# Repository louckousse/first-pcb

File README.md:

# FLATBRAIN
My first PCB, inspired by the Kyria from [Splitkb](https://splitkb.com) and the [Atreus](https://github.com/technomancy/atreus).
The goal is to get an unsplitted Kyria easily transportable.
The angle is 28° which approximatively correspond to my hand angle.

All the pcb files are created in Kicad, you can find everything in the root folder.

All the dxf files are created in Freecad, you can find everything in the case folder.
For now there is only file necessary to create pcb plate, and the kicad project associated.

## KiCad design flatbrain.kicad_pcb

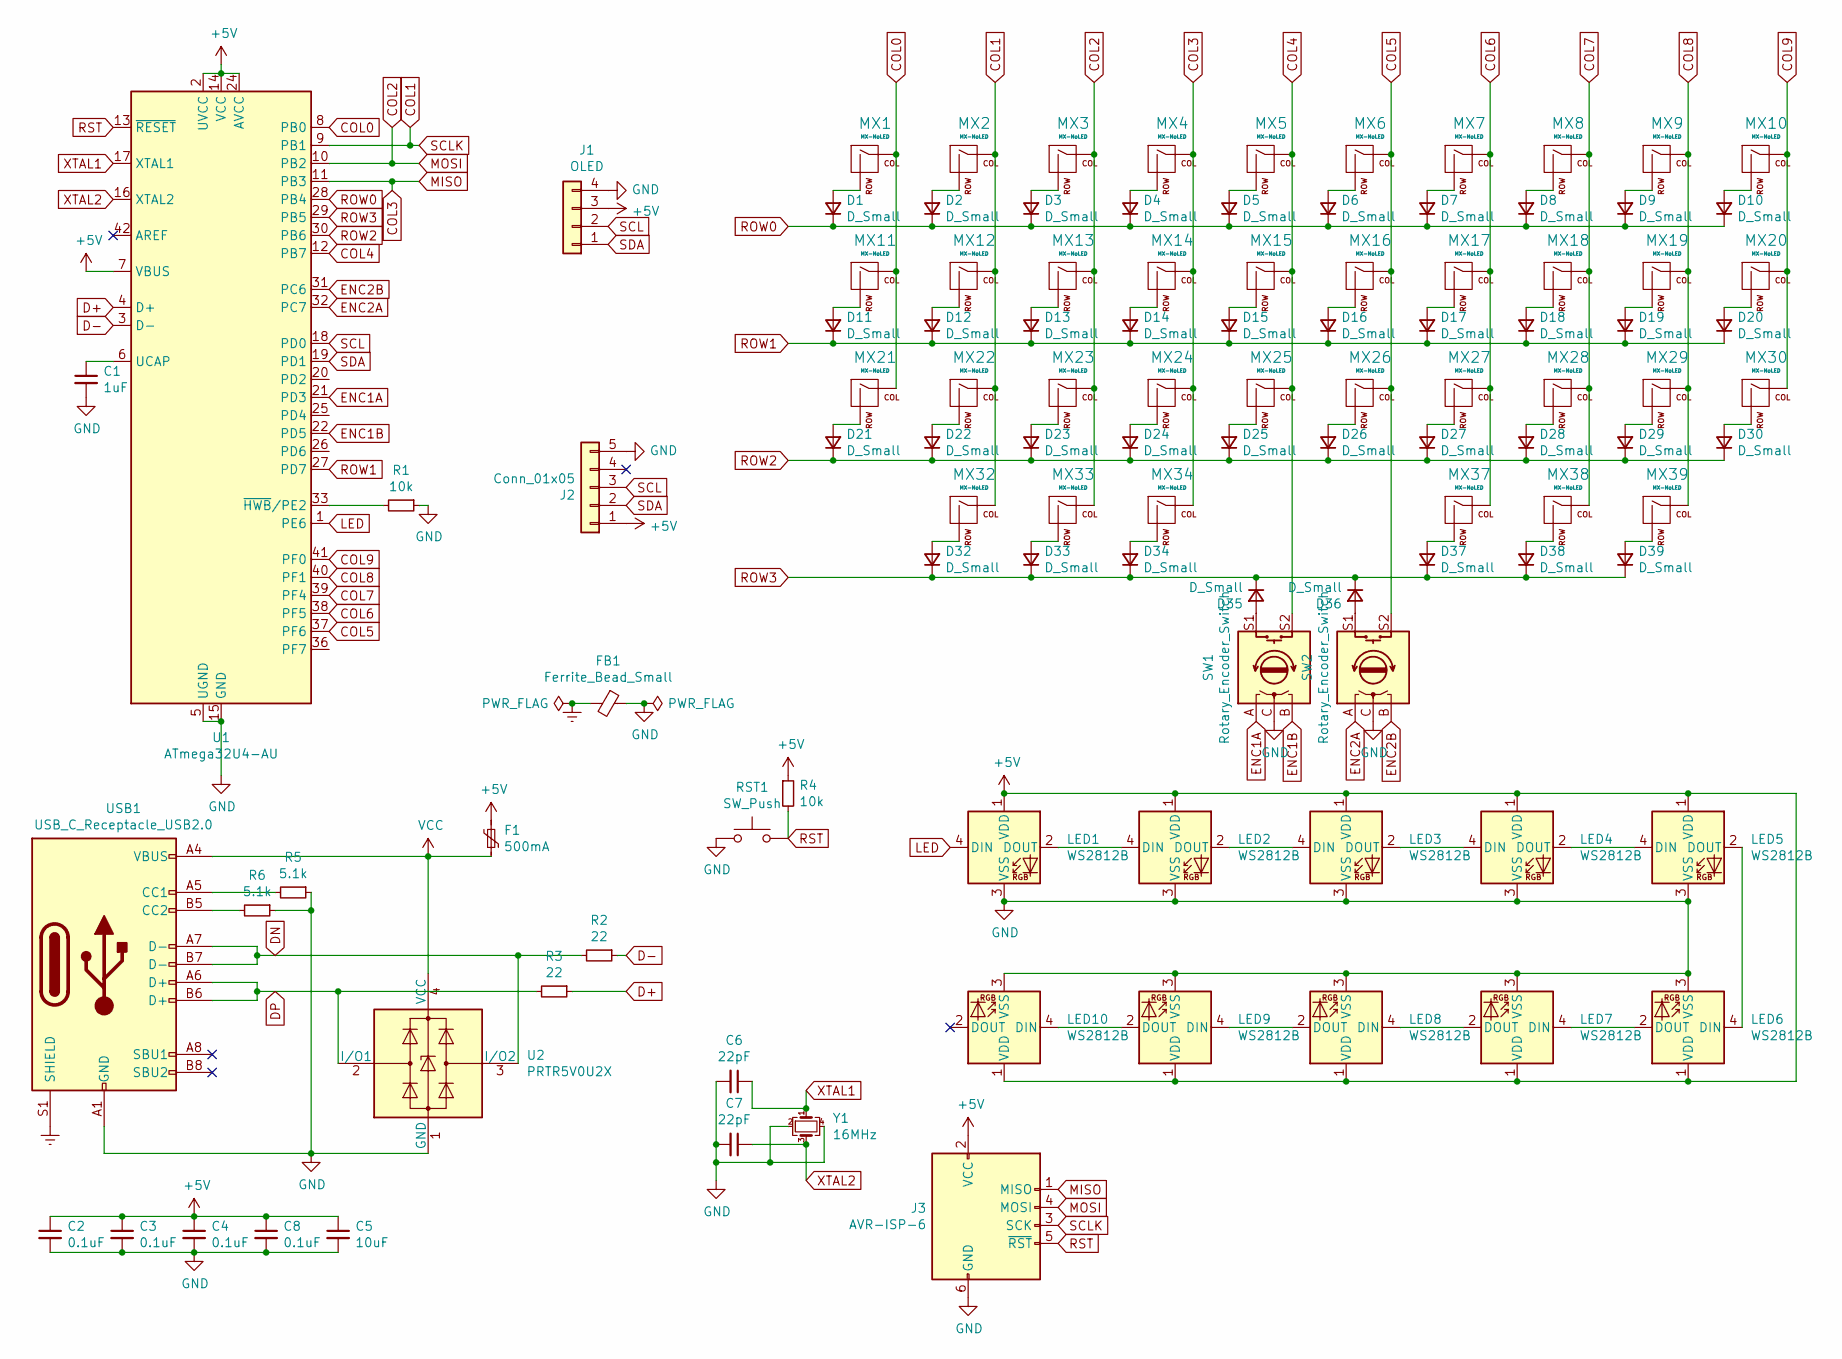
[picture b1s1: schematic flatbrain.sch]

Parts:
C1: 1uF; C_0805_2012Metric
C2, C3, C4, C8: 0.1uF; C_0805_2012Metric
C5: 10uF; C_0805_2012Metric
C6, C7: 22pF; C_0805_2012Metric
D1, D2, D3, D4, D5, D6, D7, D8, D9, D10, D11, D12, D13, D14, D15, D16, D17, D18, D19, D20, D21, D22, D23, D24, D25, D26, D27, D28, D29, D30, D32, D33, D34, D35, D36, D37, D38, D39: D_Small; Diode-Hybrid-Back
F1: 500mA; Fuse_1206_3216Metric
FB1: Ferrite_Bead_Small; L_0805_2012Metric_Pad1.15x1.40mm_HandSolder
J1: OLED; PinHeader_1x04_P2.54mm_Vertical
J2: Conn_01x05; pimoroni_trackball
J3: AVR-ISP-6; Reset_Pretty-Mask
LED1, LED2, LED3, LED4, LED5, LED6, LED7, LED8, LED9, LED10: WS2812B; LED_WS2812B_PLCC4_5.0x5.0mm_P3.2mm
MX1, MX2, MX3, MX4, MX5, MX6, MX7, MX8, MX9, MX10, MX11, MX12, MX13, MX14, MX15, MX16, MX17, MX18, MX19, MX20, MX21, MX22, MX23, MX24, MX25, MX26, MX27, MX28, MX29, MX30, MX32, MX33, MX34, MX37, MX38, MX39: MX-NoLED; mix_1u
R1, R4: 10k; R_0805_2012Metric
R2, R3: 22; R_0805_2012Metric
R5, R6: 5.1k; R_0805_2012Metric
RST1: SW_Push; SKQG-1155865
SW1, SW2: Rotary_Encoder_Switch; rotary_full
U1: ATmega32U4-AU; TQFP-44_10x10mm_P0.8mm
U2: PRTR5V0U2X; SOT143B
USB1: USB_C_Receptacle_USB2.0; USB_C_Receptacle_HRO_TYPE-C-31-M-12
Y1: 16MHz; Crystal_SMD_3225-4Pin_3.2x2.5mm

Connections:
+5V: C2.1, C3.1, C4.1, C5.1, C8.1, F1.1, J1.3, J2.1, J3.2 (VCC), LED1.1 (VDD), LED2.1 (VDD), LED3.1 (VDD), LED4.1 (VDD), LED5.1 (VDD), LED6.1 (VDD), LED7.1 (VDD), LED8.1 (VDD), LED9.1 (VDD), LED10.1 (VDD), R4.1, U1.2 (UVCC), U1.7 (VBUS), U1.14 (VCC), U1.24 (AVCC), U1.34 (VCC), U1.44 (AVCC); also elsewhere on the board
COL0: MX1.1 (COL), MX11.1 (COL), MX21.1 (COL), U1.8 (PB0)
COL1: J3.3 (SCK), MX2.1 (COL), MX12.1 (COL), MX22.1 (COL), MX32.1 (COL), U1.9 (PB1)
COL2: J3.4 (MOSI), MX3.1 (COL), MX13.1 (COL), MX23.1 (COL), MX33.1 (COL), U1.10 (PB2)
COL3: J3.1 (MISO), MX4.1 (COL), MX14.1 (COL), MX24.1 (COL), MX34.1 (COL), U1.11 (PB3)
COL4: MX5.1 (COL), MX15.1 (COL), MX25.1 (COL), SW1.S2, U1.12 (PB7)
COL5: MX6.1 (COL), MX16.1 (COL), MX26.1 (COL), SW2.S2, U1.37 (PF6)
COL6: MX7.1 (COL), MX17.1 (COL), MX27.1 (COL), MX37.1 (COL), U1.38 (PF5)
COL7: MX8.1 (COL), MX18.1 (COL), MX28.1 (COL), MX38.1 (COL), U1.39 (PF4)
COL8: MX9.1 (COL), MX19.1 (COL), MX29.1 (COL), MX39.1 (COL), U1.40 (PF1)
COL9: MX10.1 (COL), MX20.1 (COL), MX30.1 (COL), U1.41 (PF0)
D+: R3.1, U1.4 (D+)
D-: R2.1, U1.3 (D-)
DN: R2.2, U2.3 (I/O2), USB1.A7 (D-), USB1.B7 (D-)
DP: R3.2, U2.2 (I/O1), USB1.A6 (D+), USB1.B6 (D+)
ENC1A: SW1.A, U1.21 (PD3)
ENC1B: SW1.B, U1.22 (PD5)
ENC2A: SW2.A, U1.32 (PC7)
ENC2B: SW2.B, U1.31 (PC6)
Earth: FB1.2, USB1.S1 (SHIELD)
GND: C1.2, C2.2, C3.2, C4.2, C5.2, C6.2, C7.2, C8.2, FB1.1, J1.4, J2.5, J3.6 (GND), LED1.3 (VSS), LED2.3 (VSS), LED3.3 (VSS), LED4.3 (VSS), LED5.3 (VSS), LED6.3 (VSS), LED7.3 (VSS), LED8.3 (VSS), LED9.3 (VSS), LED10.3 (VSS), R1.1, R5.1, R6.1, RST1.1, SW1.C, SW2.C, U1.5 (UGND), U1.15 (GND), U1.23 (GND), U1.35 (GND), U1.43 (GND), U2.1 (GND), USB1.A1 (GND), USB1.A12 (GND), USB1.B1 (GND), USB1.B12 (GND), Y1.2, Y1.4; also elsewhere on the board
LED: LED1.4 (DIN), U1.1 (PE6)
unnamed: C1.1, U1.6 (UCAP)
unnamed: D1.2 (A), MX1.2 (ROW)
unnamed: D2.2 (A), MX2.2 (ROW)
unnamed: D3.2 (A), MX3.2 (ROW)
unnamed: D4.2 (A), MX4.2 (ROW)
unnamed: D5.2 (A), MX5.2 (ROW)
unnamed: D6.2 (A), MX6.2 (ROW)
unnamed: D7.2 (A), MX7.2 (ROW)
unnamed: D8.2 (A), MX8.2 (ROW)
unnamed: D9.2 (A), MX9.2 (ROW)
unnamed: D10.2 (A), MX10.2 (ROW)
unnamed: D11.2 (A), MX11.2 (ROW)
unnamed: D12.2 (A), MX12.2 (ROW)
unnamed: D13.2 (A), MX13.2 (ROW)
unnamed: D14.2 (A), MX14.2 (ROW)
unnamed: D15.2 (A), MX15.2 (ROW)
unnamed: D16.2 (A), MX16.2 (ROW)
unnamed: D17.2 (A), MX17.2 (ROW)
unnamed: D18.2 (A), MX18.2 (ROW)
unnamed: D19.2 (A), MX19.2 (ROW)
unnamed: D20.2 (A), MX20.2 (ROW)
unnamed: D21.2 (A), MX21.2 (ROW)
unnamed: D22.2 (A), MX22.2 (ROW)
unnamed: D23.2 (A), MX23.2 (ROW)
unnamed: D24.2 (A), MX24.2 (ROW)
unnamed: D25.2 (A), MX25.2 (ROW)
unnamed: D26.2 (A), MX26.2 (ROW)
unnamed: D27.2 (A), MX27.2 (ROW)
unnamed: D28.2 (A), MX28.2 (ROW)
unnamed: D29.2 (A), MX29.2 (ROW)
unnamed: D30.2 (A), MX30.2 (ROW)
unnamed: D32.2 (A), MX32.2 (ROW)
unnamed: D33.2 (A), MX33.2 (ROW)
unnamed: D34.2 (A), MX34.2 (ROW)
unnamed: D35.2 (A), SW1.S1
unnamed: D36.2 (A), SW2.S1
unnamed: D37.2 (A), MX37.2 (ROW)
unnamed: D38.2 (A), MX38.2 (ROW)
unnamed: D39.2 (A), MX39.2 (ROW)
unnamed: LED1.2 (DOUT), LED2.4 (DIN)
unnamed: LED2.2 (DOUT), LED3.4 (DIN)
unnamed: LED3.2 (DOUT), LED4.4 (DIN)
unnamed: LED4.2 (DOUT), LED5.4 (DIN)
unnamed: LED5.2 (DOUT), LED6.4 (DIN)
unnamed: LED6.2 (DOUT), LED7.4 (DIN)
unnamed: LED7.2 (DOUT), LED8.4 (DIN)
unnamed: LED8.2 (DOUT), LED9.4 (DIN)
unnamed: LED9.2 (DOUT), LED10.4 (DIN)
unnamed: R1.2, U1.33 (~HWB~/PE2)
unnamed: R5.2, USB1.A5 (CC1)
unnamed: R6.2, USB1.B5 (CC2)
ROW0: D1.1 (K), D2.1 (K), D3.1 (K), D4.1 (K), D5.1 (K), D6.1 (K), D7.1 (K), D8.1 (K), D9.1 (K), D10.1 (K), U1.28 (PB4)
ROW1: D11.1 (K), D12.1 (K), D13.1 (K), D14.1 (K), D15.1 (K), D16.1 (K), D17.1 (K), D18.1 (K), D19.1 (K), D20.1 (K), U1.27 (PD7)
ROW2: D21.1 (K), D22.1 (K), D23.1 (K), D24.1 (K), D25.1 (K), D26.1 (K), D27.1 (K), D28.1 (K), D29.1 (K), D30.1 (K), U1.30 (PB6)
ROW3: D32.1 (K), D33.1 (K), D34.1 (K), D35.1 (K), D36.1 (K), D37.1 (K), D38.1 (K), D39.1 (K), U1.29 (PB5)
RST: J3.5 (~RST), R4.2, RST1.2, U1.13 (~RESET)
SCL: J1.2, J2.3, U1.18 (PD0); also elsewhere on the board
SDA: J1.1, J2.2, U1.19 (PD1); also elsewhere on the board
VCC: F1.2, U2.4 (VCC), USB1.A4 (VBUS), USB1.A9 (VBUS), USB1.B4 (VBUS), USB1.B9 (VBUS)
XTAL1: C6.1, U1.17 (XTAL1), Y1.1
XTAL2: C7.1, U1.16 (XTAL2), Y1.3

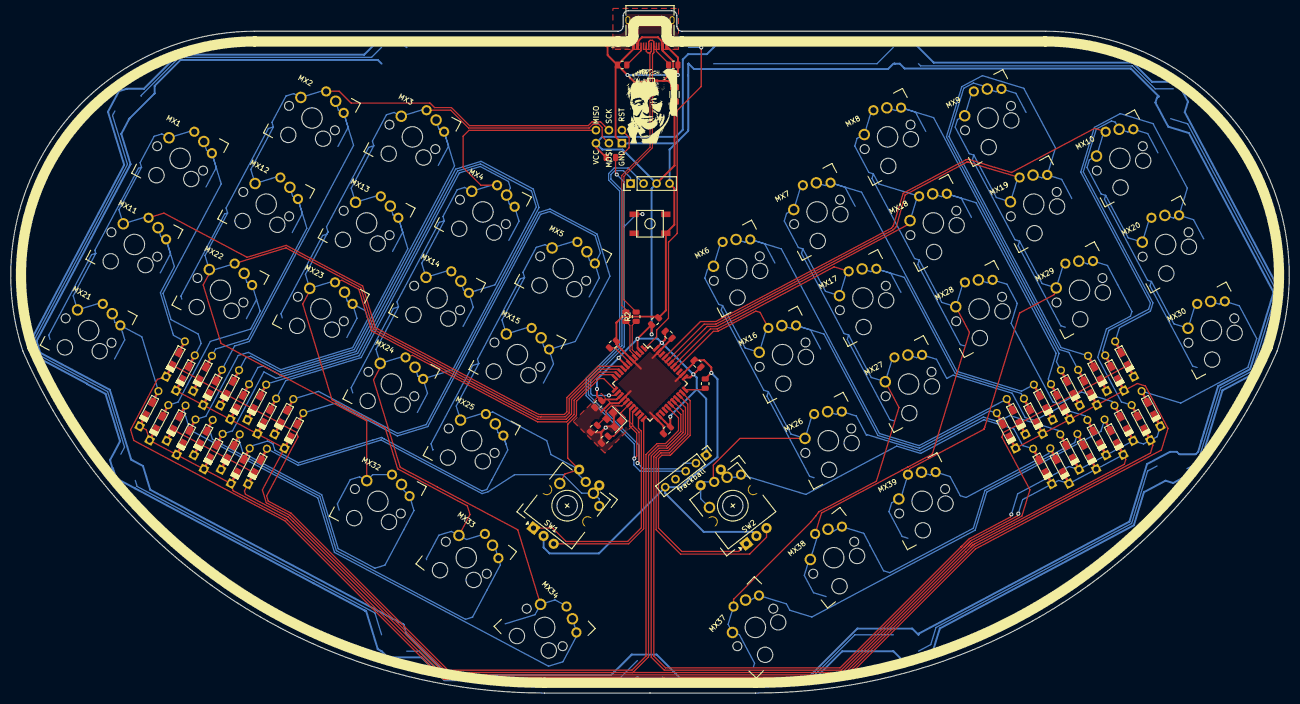
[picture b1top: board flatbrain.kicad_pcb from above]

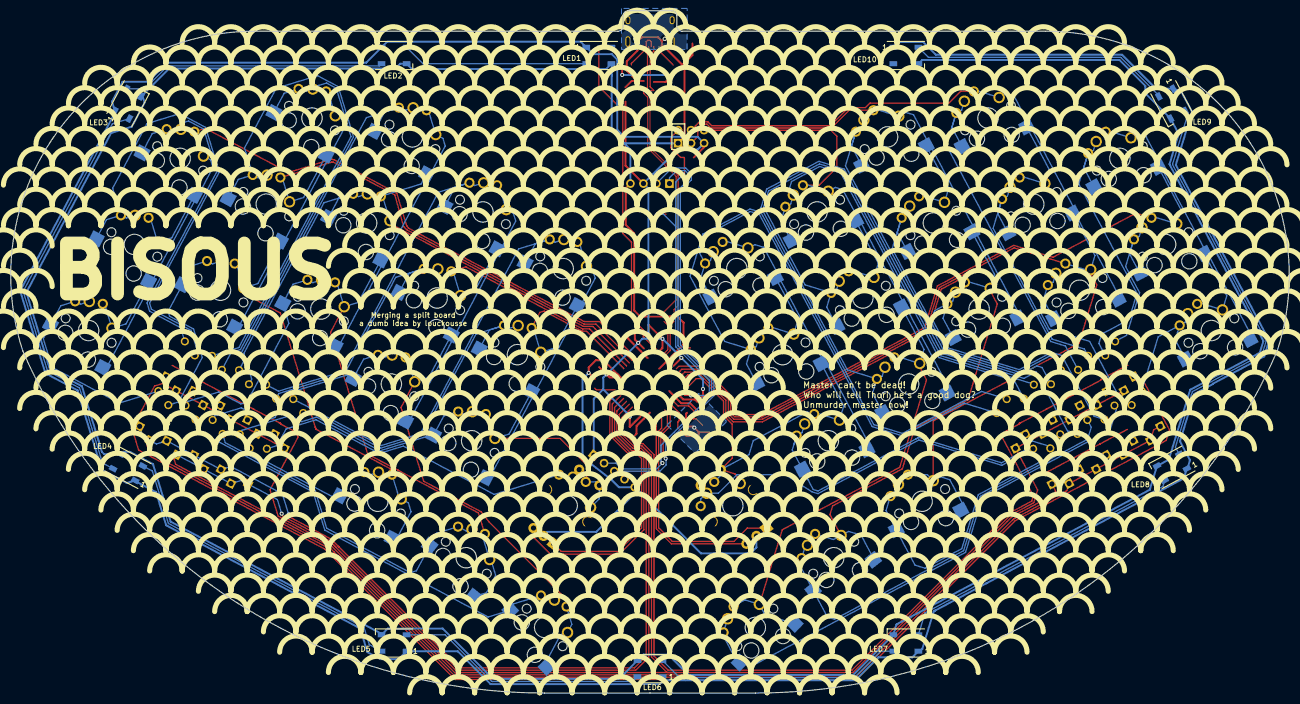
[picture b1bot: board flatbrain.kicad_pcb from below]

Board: 2 copper layers, 249.8 x 133.3 mm, 110 parts (49 on the bottom side), 83 nets.

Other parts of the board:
trackball: Conn_01x05; pimoroni_trackball

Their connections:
+5V: trackball.1; also elsewhere on the board
GND: trackball.5; also elsewhere on the board
SCL: trackball.3; also elsewhere on the board
SDA: trackball.2; also elsewhere on the board

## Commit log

2020-04-04 Init project
2020-04-04 Add the MCU
2020-04-05 Electronic schematic is over
2020-04-05 My very first pcb is over
2020-04-08 V0.0.1 of the flatbrain keyboard
2020-04-09 Replace 1u in thumb by 1.75 and 1.5
2020-04-11 Perfect alignement
2020-04-11 routing corrected
2020-04-11 realign + outline
2020-04-11 add contour.dxf
2020-04-13 final design
2020-04-14 first revision is over
2020-04-14 First revision (#1)
    First design includes 44 switch, 44 smd diodes, 1 pro-micro, 1 4-pin header for oled screen,
    outline and mounting points
    * V0.0.1 of the flatbrain keyboard
    * Replace 1u in thumb by 1.75 and 1.5
    * Perfect alignement
    * routing corrected
2020-04-14 New routing to use less pin
2020-04-15 Add LED on the schema
2020-04-15 Routing the LED
2020-04-16 Change the silks to display switch info
2020-04-16 add the plate dxf file
2020-04-16 Rename contour in bottom
2020-04-19 Version 0.1.1 (#2)
    * New routing to use less pin
    * Add LED on the schema
    * Routing the LED
    * Change the silks to display switch info
    * add the plate dxf file
    * Rename contour in bottom
2020-07-10 Add License
2020-07-10 Replace smd diode with hybrid
2020-07-10 Move all files between two folder
    PCB: contains everything pcb related
    CASE: contains everythind dxf related or non electronical
2020-07-10 Move pcb folder to get kicad import working with submodul
2020-07-10 update cache
2020-07-10 Correct the size of the switch hole
2020-07-10 Correct leds connection
2020-07-10 The routing is over jeez
2020-07-10 diode placement
2020-07-10 Remove gerber file
2020-07-10 Reroute left half
2020-07-10 Work in progress:
    Replace pro-micro with Elite-C
    Add 2 rotary encoders
2020-07-10 Update mx footprints
    TODO
    * verify the diode placement
    * replace right 1.75u with 1u + encoder
2020-07-10 Move lowest pinky keys to thumb cluster
2020-07-10 Routing is over
2020-07-10 Move down the left pinky cluster 0.25u
2020-07-10 Remove gerber files from case
2020-07-10 Update the outline with the new design
2020-07-27 a single via added to work in jlc
2020-08-16 Add choc support
2020-10-01 reverse oled pins
2020-10-03 move 0.25u the rotaries placement
2020-10-03 V0.2.0 (#3)
    * Replace smd diode with hybrid
    * Move all files between two folder
    PCB: contains everything pcb related
    CASE: contains everythind dxf related or non electronical
    * Correct the size of the switch hole
    * Move pcb folder to get kicad import working with submodul
2021-01-10 update dependencies
2021-01-10 wip: switches placed, matrix change
2021-01-13 update schema
2021-01-13 everything is placed
2021-01-14 first half done
2021-01-14 all route done
2021-01-14 update footprint
2021-01-23 update submodules
2021-01-23 rev3 is done
    add a rotary
    add silk
2021-01-24 some more silk
2021-02-06 move diode 1.5mm
2021-03-06 half pcba
2021-03-12 pcba over
2021-03-16 edge cuts
2021-04-26 ready to prod
2021-10-26 move thumb cluster
2021-11-05 routing
